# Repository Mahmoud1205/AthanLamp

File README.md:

# Athan Lamp

Hardware, software, and devlog of the Athan Lamp project.

## Special Thanks <3
I have to thank Hack Club for sponsoring this project. Specifically, Hack Club Stasis and all of the people who were involved in it. I am so grateful for this organization, and I can't describe my appreciation to them with words. Thanks Hack Club! :)

I also would like to thank the people of Fab Lab Egypt for supporting and helping me in this project in so many ways.

## Why make this project?
I recently moved to a home which is far away from a mosque, meaning I cannot hear the athan (Islamic call to prayer) anymore. I could've solve this by installing an athan application on my phone, but I can do better.

So I got the idea of making a device that's placed in my house and can play an athan sound during the athan time according to my location, this device also acts as a lamp because it controls a LED strip.

## More info!
I would like to keep this main README short, but check out the `Journal.md` file for a dev log of the whole project from start to finish!

[Showcase of the Athan Lamp project (ignore this; it's only for Hack Club Stasis qualification)](https://youtu.be/jqDg8A2GP44)

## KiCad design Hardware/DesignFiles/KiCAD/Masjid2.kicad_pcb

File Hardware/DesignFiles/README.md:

# Design Files

The hardware design files currently available are the KiCAD files and the BOM.

## Notes and Instructions
**These instructions are for fabricating the PCB manually using a CNC machine. Please ignore these instructions if you will order the PCB from a manufacturer.**
* Dont forget to add two alignment nails to help in flipping the PCB. I made space on the bottom side of the PCB for nails. Make sure to keep the nails at equal distance from the PCB corners so both PCB layers are aligned perfectly.
* Use a 0.3mm or smaller V-bit.
* Make sure the PCB is perfectly flat on the bed.
* Remember to only use 3 of the nails which are outside the PCB area, because you must remove the nail which is at the CNC origin point so the drill bit doesn't cut the nail and be damaged.
* Remember to remove the alignment nails when milling so the drill bit doesn't cut the nail and be damaged.

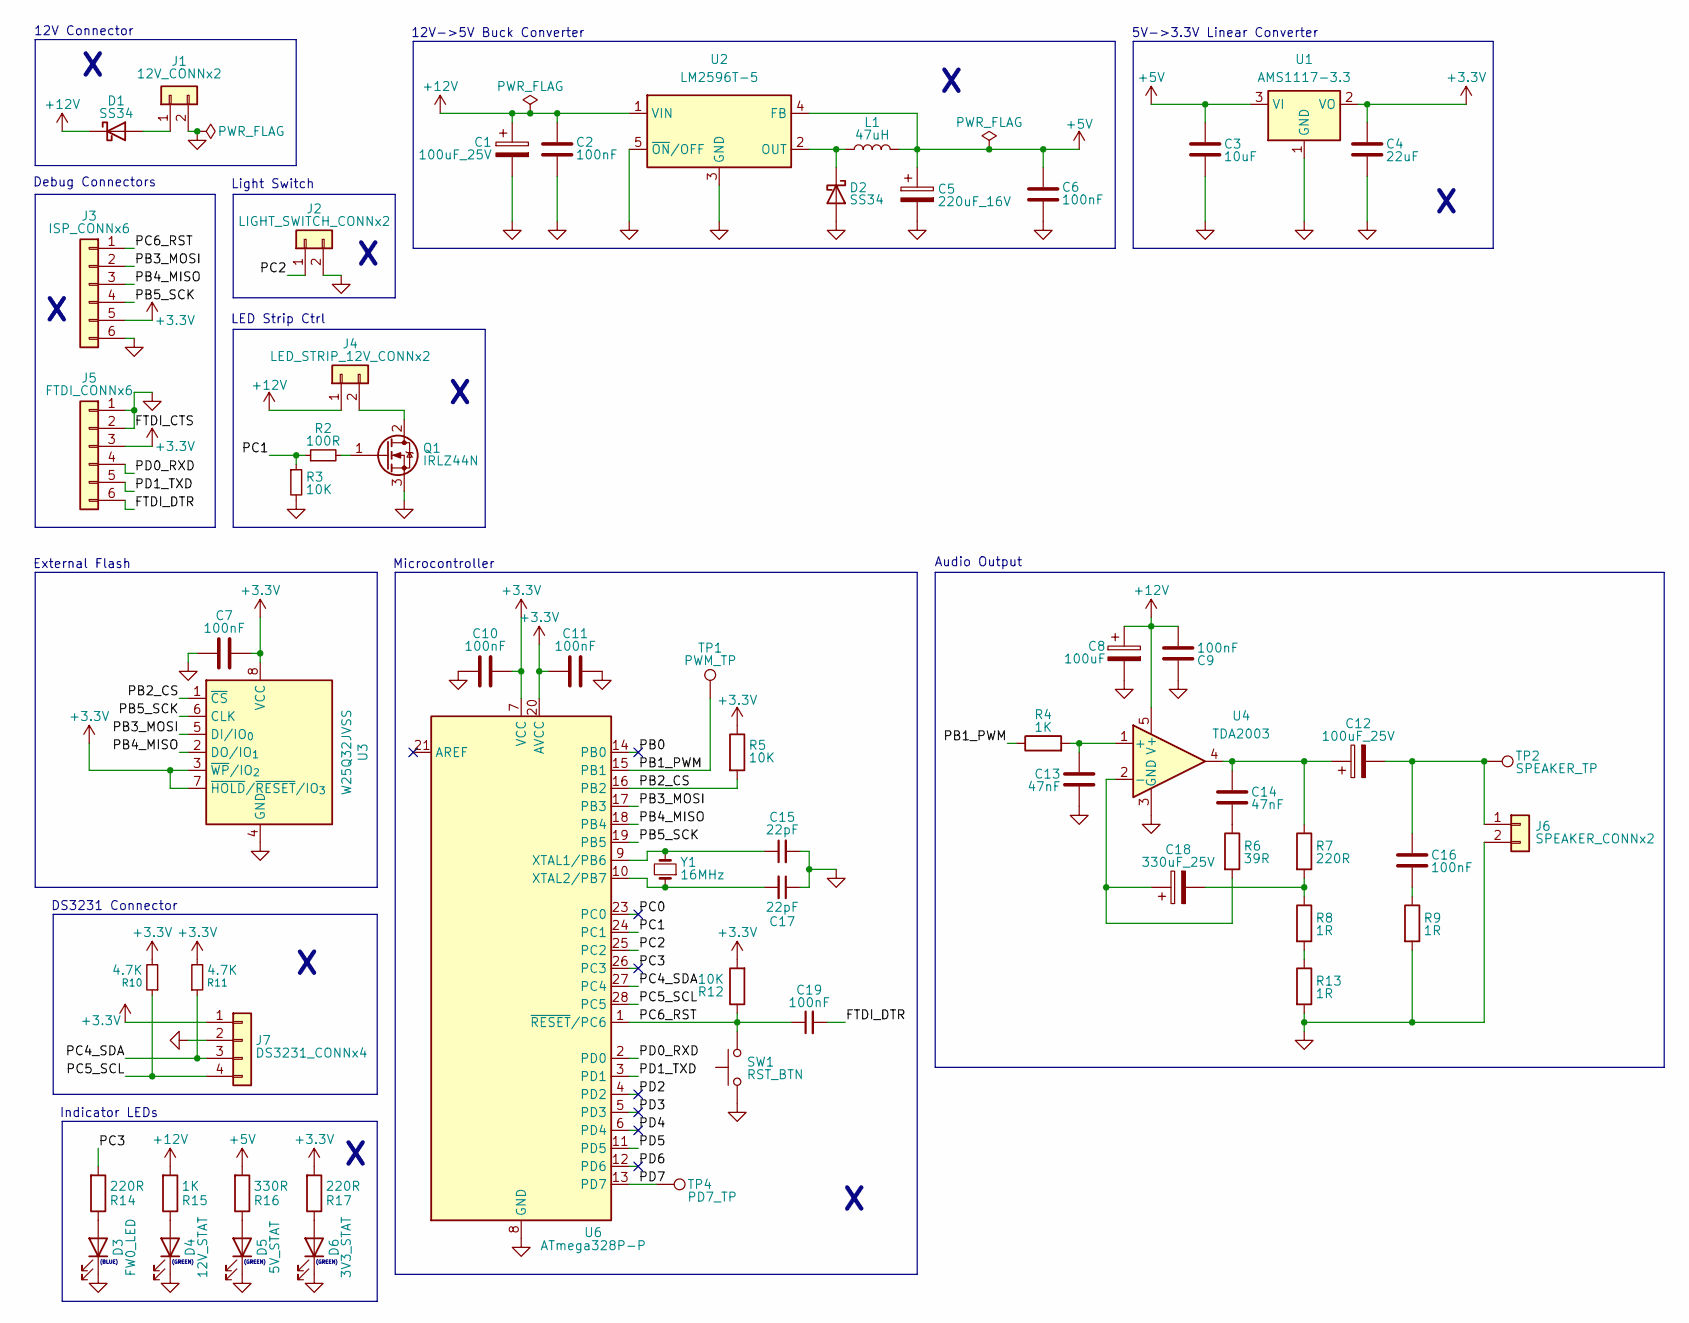
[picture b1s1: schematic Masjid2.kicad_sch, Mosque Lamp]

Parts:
C1, C12: 100uF_25V; CP_Radial_D5.0mm_P2.50mm
C2, C6, C7, C9, C10, C11, C16, C19: 100nF; C_0805_2012Metric
C3: 10uF; CP_Radial_D4.0mm_P2.00mm
C4: 22uF; CP_Radial_D6.3mm_P2.50mm
C5: 220uF_16V; CP_Radial_D8.0mm_P3.80mm
C8: 100uF; CP_Radial_D5.0mm_P2.50mm
C13, C14: 47nF; C_0805_2012Metric
C15, C17: 22pF; C_0805_2012Metric
C18: 330uF_25V; CP_Radial_D8.0mm_P3.80mm
D1, D2: SS34; D_SMA
D3: FW0_LED; LED_0805_2012Metric_Pad1.15x1.40mm_HandSolder
D4: 12V_STAT; LED_0805_2012Metric_Pad1.15x1.40mm_HandSolder
D5: 5V_STAT; LED_0805_2012Metric_Pad1.15x1.40mm_HandSolder
D6: 3V3_STAT; LED_0805_2012Metric_Pad1.15x1.40mm_HandSolder
J1: 12V_CONNx2; SolderWire-0.1sqmm_1x02_P3.6mm_D0.4mm_OD1mm
J2: LIGHT_SWITCH_CONNx2; SolderWire-0.1sqmm_1x02_P3.6mm_D0.4mm_OD1mm
J3: ISP_CONNx6; PinHeader_1x06_P2.54mm_Vertical
J4: LED_STRIP_12V_CONNx2; SolderWire-0.1sqmm_1x02_P3.6mm_D0.4mm_OD1mm
J5: FTDI_CONNx6; PinHeader_1x06_P2.54mm_Vertical
J6: SPEAKER_CONNx2; SolderWire-0.1sqmm_1x02_P3.6mm_D0.4mm_OD1mm
J7: DS3231_CONNx4; SolderWire-0.1sqmm_1x04_P3.6mm_D0.4mm_OD1mm
L1: 47uH; L_Taiyo-Yuden_MD-3030
Q1: IRLZ44N; TO-220-3_Vertical
R2: 100R; R_0603_1608Metric
R3, R5, R12: 10K; R_0805_2012Metric
R4, R15: 1K; R_0805_2012Metric
R6: 39R; R_1206_3216Metric
R7, R14, R17: 220R; R_0805_2012Metric
R8, R9, R13: 1R; R_0805_2012Metric
R10, R11: 4.7K; R_0805_2012Metric
R16: 330R; R_0805_2012Metric
SW1: RST_BTN; SW_PUSH_6mm_H4.3mm
TP1: PWM_TP; TestPoint_Pad_2.0x2.0mm
TP2: SPEAKER_TP; TestPoint_Pad_2.0x2.0mm
TP4: PD7_TP; TestPoint_Pad_2.0x2.0mm
U1: AMS1117-3.3; SOT-223-3_TabPin2
U2: LM2596T-5; TO-220-5_P3.4x3.7mm_StaggerOdd_Lead3.8mm_Vertical
U3: W25Q32JVSS; SOIC-8_5.3x5.3mm_P1.27mm
U4: TDA2003; TO-220-5_P3.4x3.7mm_StaggerEven_Lead3.8mm_Vertical
U6: ATmega328P-P; DIP-28_W7.62mm
Y1: 16MHz; Crystal_HC49-4H_Vertical

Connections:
+3.3V: C4.1, C7.2, C10.2, C11.2, J3.5, J5.3, J7.1, R5.1, R10.2, R11.2, R12.2, R17.2, U1.2 (VO), U3.3 (~WP/IO_{2}), U3.7 (~HOLD/~RESET/IO_{3}), U3.8 (VCC), U6.7 (VCC), U6.20 (AVCC)
+5V: C3.1, C5.1, C6.1, L1.2, R16.2, U1.3 (VI), U2.4 (FB)
+12V: C1.1, C2.1, C8.1, C9.2, D1.1 (K), J4.1, R15.2, U2.1 (VIN), U4.5 (V+)
/FTDI_DTR: C19.2, J5.6
/PB0: U6.14 (PB0)
/PB1_PWM: R4.1, TP1.1, U6.15 (PB1); also elsewhere on the board
/PB2_CS: R5.2, U3.1 (~CS), U6.16 (PB2)
/PB3_MOSI: J3.2, U3.5 (DI/IO_{0}), U6.17 (PB3)
/PB4_MISO: J3.3, U3.2 (DO/IO_{1}), U6.18 (PB4)
/PB5_SCK: J3.4, U3.6 (CLK), U6.19 (PB5)
/PC0: U6.23 (PC0)
/PC1: R2.1, R3.1, U6.24 (PC1)
/PC2: J2.1, U6.25 (PC2)
/PC3: R14.2, U6.26 (PC3)
/PC4_SDA: J7.3, R11.1, U6.27 (PC4)
/PC5_SCL: J7.4, R10.1, U6.28 (PC5)
/PC6_RST: C19.1, J3.1, R12.1, SW1.1, U6.1 (~RESET/PC6)
/PD0_RXD: J5.4, U6.2 (PD0)
/PD1_TXD: J5.5, U6.3 (PD1)
/PD2: U6.4 (PD2)
/PD3: U6.5 (PD3)
/PD4: U6.6 (PD4)
/PD5: U6.11 (PD5)
/PD6: U6.12 (PD6)
/PD7: TP4.1, U6.13 (PD7); also elsewhere on the board
GND: C1.2, C2.2, C3.2, C4.2, C5.2, C6.2, C7.1, C8.2, C9.1, C10.1, C11.1, C13.1, C15.2, C17.1, D2.2 (A), D3.1 (K), D4.1 (K), D5.1 (K), D6.1 (K), J1.2, J2.2, J3.6, J5.1, J5.2, J6.2, J7.2, Q1.3 (S), R3.2, R9.2, R13.2, SW1.2, U1.1 (GND), U2.3 (GND), U2.5 (~ON/OFF), U3.4 (GND), U4.3 (GND), U6.8 (GND), U6.22 (GND)
unnamed: C12.1, C14.1, R7.1, U4.4
unnamed: C14.2, R6.1
unnamed: C16.2, R9.1
unnamed: C18.2, R7.2, R8.1
unnamed: D1.2 (A), J1.1
unnamed: D2.1 (K), L1.1, U2.2 (OUT)
unnamed: D3.2 (A), R14.1
unnamed: D4.2 (A), R15.1
unnamed: D5.2 (A), R16.1
unnamed: D6.2 (A), R17.1
unnamed: J4.2, Q1.2 (D)
unnamed 37: C12.2, C16.1, J6.1, TP2.1; also elsewhere on the board
unnamed: Q1.1 (G), R2.2
unnamed: R8.2, R13.1
unnamed: C13.2, R4.2, U4.1 (+)
unnamed: C18.1, R6.2, U4.2 (-)
unnamed: C15.1, U6.9 (XTAL1/PB6), Y1.2
unnamed: C17.2, U6.10 (XTAL2/PB7), Y1.1

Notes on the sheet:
LED Strip Ctrl
Debug Connectors
(GREEN)
Audio Output
12V->5V Buck Converter
(BLUE)
12V Connector
Microcontroller
5V->3.3V Linear Converter
Indicator LEDs
External Flash
Light Switch
DS3231 Connector

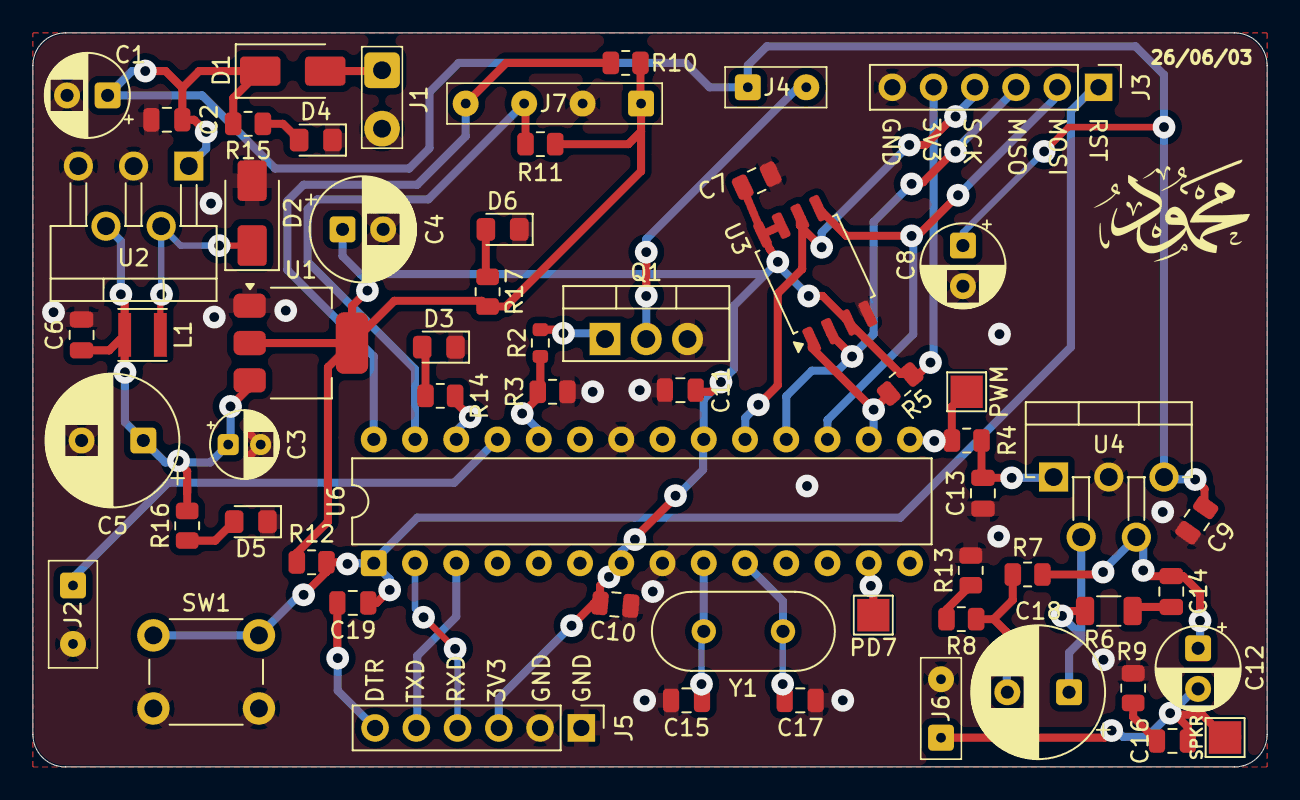
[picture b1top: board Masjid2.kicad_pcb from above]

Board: 2 copper layers, 76.0 x 45.2 mm, 60 parts (0 on the bottom side), 37 nets.

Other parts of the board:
PD7: PD7_TP; TestPoint_Pad_2.0x2.0mm
PWM: PWM_TP; TestPoint_Pad_2.0x2.0mm
SPKR: SPEAKER_TP; TestPoint_Pad_2.0x2.0mm

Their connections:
/PB1_PWM: PWM.1 (1_1); also elsewhere on the board
/PD7: PD7.1 (1_1); also elsewhere on the board
unnamed 37: SPKR.1 (1_1); also elsewhere on the board

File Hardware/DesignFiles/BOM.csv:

#,References,Value,Footprint,Quantity,Price (approx.)
1,"C2, C6, C7, C9, C10, C11, C16, C19","100nF","C_0805_2012Metric",8,0.15
2,"C1, C12","100uF_25V","CP_Radial_D5.0mm_P2.50mm",2,0.038
3,"C13, C14","47nF","C_0805_2012Metric",2,0.038
4,"C15, C17","22pF","C_0805_2012Metric",2,0.038
5,"C3","10uF","CP_Radial_D4.0mm_P2.00mm",1,0.019
6,"C4","22uF","CP_Radial_D6.3mm_P2.50mm",1,0.019
7,"C5","220uF_16V","CP_Radial_D8.0mm_P3.80mm",1,0.019
8,"C8","100uF","CP_Radial_D5.0mm_P2.50mm",1,0.019
9,"C18","330uF_25V","CP_Radial_D8.0mm_P3.80mm",1,0.019
10,"R1, R8, R9, R13","1R","R_0805_2012Metric",4,0.0152
11,"R3, R5, R12","10K","R_0805_2012Metric",3,0.0114
12,"R7, R14, R17","220R","R_0805_2012Metric",3,0.0114
13,"R4, R15","1K","R_0805_2012Metric",2,0.0076
14,"R10, R11","4.7K","R_0805_2012Metric",2,0.0076
15,"R2","100R","R_0603_1608Metric",1,0.0038
16,"R6","39R","R_1206_3216Metric",1,0.0038
17,"R16","330R","R_0805_2012Metric",1,0.0038
18,"L1","47uH","L_Taiyo-Yuden_MD-3030",1,0.13
19,"D1, D2","SS34","D_SMA",2,0.19
20,"D3","FW0_LED","LED_0805_2012Metric_Pad1.15x1.40mm_HandSolder",1,0.015
21,"D4","12V_STAT","LED_0805_2012Metric_Pad1.15x1.40mm_HandSolder",1,0.015
22,"D5","5V_STAT","LED_0805_2012Metric_Pad1.15x1.40mm_HandSolder",1,0.015
23,"D6","3V3_STAT","LED_0805_2012Metric_Pad1.15x1.40mm_HandSolder",1,0.015
24,"U1","AMS1117-3.3","SOT-223-3_TabPin2",1,0.038
25,"U2","LM2596T-5","TO-220-5_P3.4x3.7mm_StaggerOdd_Lead3.8mm_Vertical",1,0.57
26,"U3","W25Q32JVSS","SOIC-8_5.3x5.3mm_P1.27mm",1,0.95
27,"U4","TDA2003","TO-220-5_P3.4x3.7mm_StaggerEven_Lead3.8mm_Vertical",1,0.23
28,"U5","ATmega328P-A","TQFP-32_7x7mm_P0.8mm",1,2.55
29,"Y1","16MHz","Crystal_HC49-4H_Vertical",1,0.057
30,"SW1","RST_BTN","SW_PUSH_6mm_H4.3mm",1,0.014
31,"Q1","IRLZ44N","TO-220-3_Vertical",1,0.85
33,"J2","LIGHT_SWITCH_CONNx2","SolderWire-0.1sqmm_1x02_P3.6mm_D0.4mm_OD1mm",1,0.047
34,"J3","ISP_CONNx6","PinHeader_1x06_P2.54mm_Vertical",1,0.019
35,"J4","LED_STRIP_12V_CONNx2","SolderWire-0.1sqmm_1x02_P3.6mm_D0.4mm_OD1mm",1,1.89
36,"J5","FTDI_CONNx6","PinHeader_1x06_P2.54mm_Vertical",1,0.019
37,"J6","SPEAKER_CONNx2","SolderWire-0.1sqmm_1x02_P3.6mm_D0.4mm_OD1mm",1,1.13
38,"J7","DS3231_CONNx4","SolderWire-0.1sqmm_1x04_P3.6mm_D0.4mm_OD1mm",1,1.70
38,"N/A","PAM8403","MODULE",1,0.61

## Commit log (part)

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2026-04-23 edit readme
2026-04-23 fix video embed
2026-04-23 try again to fix video embed
2026-04-23 explain arabic in video
2026-04-23 Highlight timer message in Arabic in README
    Updated README to emphasize the timer's Arabic message.
2026-04-23 some of hardware README
2026-04-23 add pcb attempts gif
2026-04-23 finish hardware README
2026-04-23 fix videos embed
2026-04-23 add design files readme
2026-04-23 add software readme and first athan calculation prototype in C
2026-04-23 try to fix video link again
2026-04-23 fix and update READMEs and add pcb hardware design files
2026-04-23 add BOM
2026-04-24 add BOM for stasis program, fix READMEs, add more images to README
2026-04-24 fix BOM for stasis
2026-04-24 add PCB .step
2026-04-24 add BOM to README
2026-04-24 small changes to hardware README
2026-04-27 remove stasis note
2026-05-05 add pcb production files
2026-05-15 fix for stasis
2026-06-29 update readme, upload real firmware
2026-06-29 ready for stasis build review
